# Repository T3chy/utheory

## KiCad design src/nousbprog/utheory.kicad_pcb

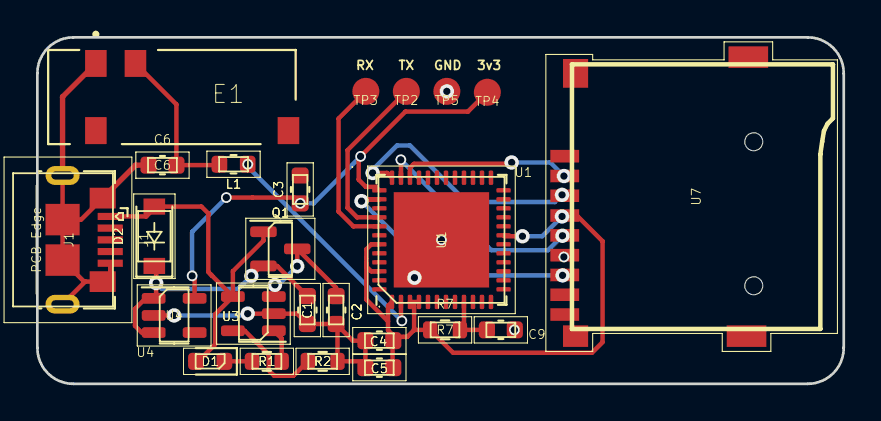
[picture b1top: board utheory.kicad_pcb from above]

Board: 2 copper layers, 44.8 x 19.2 mm, 24 parts (0 on the bottom side), 17 nets.

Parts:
C1: 1uF; C_0603_1608Metric
C2: 10uF; C_0603_1608Metric
C3: 2.2uF; C_0603_1608Metric
C4, C5: 0.1uF; C_0603_1608Metric
C6, C9: 2.7pF; C_0603_1608Metric
D1: RED_LED; LED_0603_1608Metric
D2: D_Schottky; D_SOD-123
E1: PRO-OB-440; ANT_PRO-OB-440
J1: USB_B_Micro; USB_Micro-B_GCT_USB3076-30-A
L1: 1.8nH; L_0603_1608Metric
Q1: FDN340P; SOT-23
R1: 2k; R_0603_1608Metric
R2, R7: 10k; R_0603_1608Metric
TP2: rxdct; testpad
TP3: txdct; testpad
TP4, TP5: TestPoint; testpad
U1: ESP32-PICO-D4; QFN-48-1EP_7x7mm_P0.5mm_EP5.3x5.3mm
U3: SL4054ST25P; SOT-23-5
U4: SE5218ALG-LF; SOT-23-5
U7: MicroSD_SPI_CD; GCT-MEM2055-00-190-01-A

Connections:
+3V3: C3.1, C4.1, C5.1, R7.1, TP4.1, U1.1, U1.3, U1.4, U1.19, U1.37, U1.43, U1.46, U4.5, U7.4
CLK: U1.35, U7.5
CS: U1.34, U7.2
EN: C9.1, R7.2, U1.9
GND: C1.2, C2.2, C3.2, C4.2, C5.2, C6.1, C9.2, E1.1, J1.5, J1.6, R2.2, TP5.1, U1.49, U3.2, U4.2, U7.6
MISO: U1.38, U7.7
MOSI: U1.36, U7.3
unnamed: C1.1, D2.1, Q1.2, U4.1, U4.3
unnamed: C6.2, E1.2, L1.2
unnamed: D1.1, R1.2
unnamed: D1.2, D2.2, J1.1, Q1.1, U3.4
unnamed: L1.1, U1.2
unnamed: R1.1, U3.1
unnamed: R2.1, U3.5
RXD: TP2.1, U1.40
TXD: TP3.1, U1.41
VBAT: C2.1, Q1.3, U3.3

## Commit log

2021-06-16 schematic more filled out
2021-06-16 Create LICENSE
2021-06-17 pcb v1
2021-06-17 added antenna
2021-06-17 cheapo version without usb uart bridge
2021-06-17 forgot to delete these whoops
